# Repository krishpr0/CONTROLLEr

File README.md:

# CONTROLLER

CONTROLLER, IT is an Circuit which allows any type of SSD/HDD of a laptop size which is 2.5 inch Memory be a External Storage. This Project main chip is the ASM2464PD due to its high speed transfer speed. This chip was selected due to its support of USB4/Thunderbolt.

## What is this Project?
Controller is a high speed transfer external circuit board which is meant to make any 2.5 inch hard drive or ssd into an external Storage system. This unlocks the ability to make our own external storage system rather then buying it from outside. 

## How do we use Controller?
- First of all there are 4 screws on the side 2 on each unscrew it!
- Then pull of the top cover off the base plate.
- Then insert and slide in the HDD/SSD onto the PCIe connector.
- Place the cover plate back on and then tighten the screw 2 on each side this should secure the storage as well as the top case.
- Then connect to the computer that's it!
- (*NOTE: SOME MAY REQUIRE TO FLASH A FIRMWARE*)

## The reason for building this
Nowadays the software programs are increasing in size and as the phoots, videos we click also getting bigger and bigger. In my case each of my photos clicked is more than 5MB so that storage would rlly quickly fill up and I had to either delete it or buy an external drive and store it there.!

And so I choose the 2nd opt buy and external drive to store it cuz why delete photos which is memoory.!
So yeh like that it went on for years and years pile of drives js filled with photos, videos and files but now the storage are getting more expensier and also the casing used to hold the drive. !

SO i was really frustraied atp And i thought abt is there a way to make a good external drive !?
SO that was the reason i started this project due to the rise in price of storage due to AI>
T-T

## CAD

## CIRCUIT DIAGRAM: 

## PCB

## PCB 3D

# BOM
| #  | Reference                             | Value                                    | Footprint                       | Qty | Unit (USD) | Total (USD) | Datasheet / Link                                                                              |
|----|---------------------------------------|------------------------------------------|---------------------------------|-----|------------|-------------|-----------------------------------------------------------------------------------------------|
| 1  | U1                                    | ASM2464PD  USB4 Host Controller          | ASM2464PD                       | 1   | $8.000     | $8.000      | https://www.asmedia.com.tw/product/aGaq3YfSP5Yrq0T0/cGaq7XeSw9YRQ5T1                          |
| 2  | U2                                    | SPI Flash  SOIC-8  (Firmware storage)    | SOIC-8_5.3x5.3mm_P1.27mm        | 1   | $3         | $3          | http://ww1.microchip.com/downloads/en/DeviceDoc/21832H.pdf                                    |
| 3  | U3                                    | SPI Flash  DFN-8  (Firmware storage)     | DFN-8-1EP_3x2mm_P0.5mm          | 1   | $3         | $3          | http://ww1.microchip.com/downloads/en/DeviceDoc/21832H.pdf                                    |
| 4  | Y1                                    | 25MHz Crystal  SMD 3225-4Pin             | Crystal_SMD_3225-4Pin_3.2x2.5mm | 1   | $0.350     | $0.350      | https://au.rs-online.com/web/p/crystal-units/9047531                                          |
| 5  | J1                                    | USB-C Receptacle  Amphenol 12401610E4-2A | USB_C_Receptacle_Amphenol       | 1   | $1.200     | $1.200      | https://www.usb.org/sites/default/files/documents/usb_type-c.zip                              |
| 6  | J2                                    | SPI Header  2x04  2.54mm                 | PinHeader_2x04                  | 1   | $0.100     | $0.100      | ---                                                                                           |
| 7  | J3                                    | PCIe x4 Connector  THT Open              | PCIe_x4_tht_open                | 1   | $1.500     | $1.500      | http://www.ritrontek.com/uploadfile/2016/1026/20161026105231124.pdf                           |
| 8  | J4                                    | Chip Annoyers Header  2x02  2.54mm       | PinHeader_2x02                  | 2   | $0.10      | $0.10       | https://www.digikey.com/en/products/detail/harwin-inc/M20-9990246/3728226                     |
| 9  | J5                                    | UART Header  1x04  2.54mm                | PinHeader_1x04                  | 1   | $0.10      | $0.050      | https://www.digikey.com/en/products/detail/jst-sales-america-inc/B4B-XH-A/1651047             |
| 10 | J6                                    | I2C Header  1x04  2.54mm                 | PinHeader_1x04                  | 1   | $0.10      | $0.050      | https://www.digikey.com/en/products/detail/jst-sales-america-inc/B4B-XH-A/1651047             |
| 11 | J7,J8,J9,J10                          | 1x06 Header  1.27mm  x4                  | PinHeader_1x06                  | 4   | $0.20      | $0.200      | https://www.digikey.in/en/products/detail/jst-sales-america-inc/B6B-PH-K-S/926615             |
| 12 | R1,R2,R20,R24,R26,R29,R39,R41,R42,R43 | 1k ohm  0402                             | R_0402_1005Metric               | 10  | $0.15      | $1.50       | https://www.digikey.com.au/en/products/detail/yageo/RC0402FR-071KL/726513                     |
| 13 | R3,R4,R5,R6,R7,R8,R25,R30,R31         | 0 ohm  0402                              | R_0402_1005Metric               | 9   | $0.15      | $1.35       | https://www.digikey.com.au/en/products/detail/yageo/RC0402JR-070RL/726406                     |
| 14 | R9,R27,R28,R35,R38,R34,R36,R37        | 4.7k ohm  0402                           | R_0402_1005Metric               | 8   | $0.15      | $0.75       | https://www.digikey.com.au/en/products/detail/yageo/RC0402JR-074K7L/726477                    |
| 15 | R10,R21,R22, R23                      | 10k ohm  0402                            | R_0201_0603Metric               | 4   | $0.15      | $0.60       | https://www.digikey.com.au/en/products/detail/vishay-dale/CRCW040210K0FKED/1178121            |
| 16 | R11,R12,R13,R14,R15,R16,R17,R18       | 220k ohm  0201                           | R_0201_0603Metric               | 8   | $0.15      | $1.20       | https://www.digikey.com/en/products/detail/yageo/RC0201JR-07220KP/15219948                    |
| 19 | R32                                   | 12.1k ohm  0402                          | R_0402_1005Metric               | 1   | $0.10      | $0.10       | https://www.digikey.in/en/products/detail/yageo/RC0402FR-1012K1L/17020868                     |
| 20 | R33                                   | 100k ohm  0402                           | R_0402_1005Metric               | 1   | $0.20      | $0.20       | https://www.digikey.com/en/products/detail/yageo/AT0402BRD07100KL/5138605                     |
| 22 | C1                                    | 10pF  0402                               | C_0402_1005Metric               | 1   | $0.10      | $0.10       | https://www.digikey.com/en/products/detail/yageo/CC0402JRNPO8BN100/5883266                    |
| 23 | C2,C3,C4,C5,C6,C7,C8,C9               | 330nF  0201                              | C_0201_0603Metric               | 8   | $0.10      | $0.80       | https://www.mouser.in/ProductDetail/Walsin/0201X334M6R3CT?qs=iLbezkQI%252Bsj6TtN1Mk8apQ%3D%3D |
| 24 | C10,C21                               | 1uF  0402                                | C_0402_1005Metric               | 2   | $0.01      | $0.02       | https://robu.in/product/1uf-capacitor-smdc-0402-pack-of-50/                                   |
| 25 | C11                                   | 220pF  0402  DNP                         | C_0402_1005Metric               | 1   | $0.10      | $0.10       | https://www.digikey.com/en/products/detail/yageo/CC0402GRNPO9BN221/5883253                    |
| 26 | C12,C13,C14,C15,C16,C17,C18,C19       | 220nF  0402                              | C_0402_1005Metric               | 8   | $0.003     | $0.024      | https://www.lcsc.com/product-detail/C2649521.html                                             |
| 27 | C20                                   | 100nF  0402                              | C_0402_1005Metric               | 1   | $0.003     | $0.003      | https://www.lcsc.com/product-detail/C60474.html                                               |
| 28 | D1,D2,D3,D4,D5,D6,D7,D8               | Diode  0201  DNP                         | D_0201_0603Metric               | 8   | $0.32      | $2.56       | https://www.digikey.in/en/products/detail/kyocera-avx/GG020105100N2P/6826542                  |
| 29 | D9,D10,D11,D12,D13,D14,D15,D16        | LED  0603                                | LED_0603_1608Metric             | 8   | $0.01      | $0.08       | https://www.lcsc.com/product-detail/C19171390.html                                            |
|    | TOTAL                                 |                                          |                                 |     |            | 15.462      |                                                                                               |

# HOW TO BUILD

## What you need
-  Soldering Iron
-  Soldering wire
-  Flux
-  Multimeter
-  USB-C Cable

### Assembly Order
1. Solder all SMD Passives first (Resistors, Capacitors)
2. Solder ICs
3. Solder USB-C
4. Connect the PCIe Connecotr
5. Connect the Drive
6. Plug and Transfer.

### Firmware Setup 
- Open the 'firmware/src' - Upload the whole program to the SPI
- RUN

# Feature
- 1MB ROM
- SPI
- 40 GBPS USB Transfer Speed
- USB4/Thuerbolt Support
- HHD/SSD/NVMe support
- USB-C
- Power effiecent

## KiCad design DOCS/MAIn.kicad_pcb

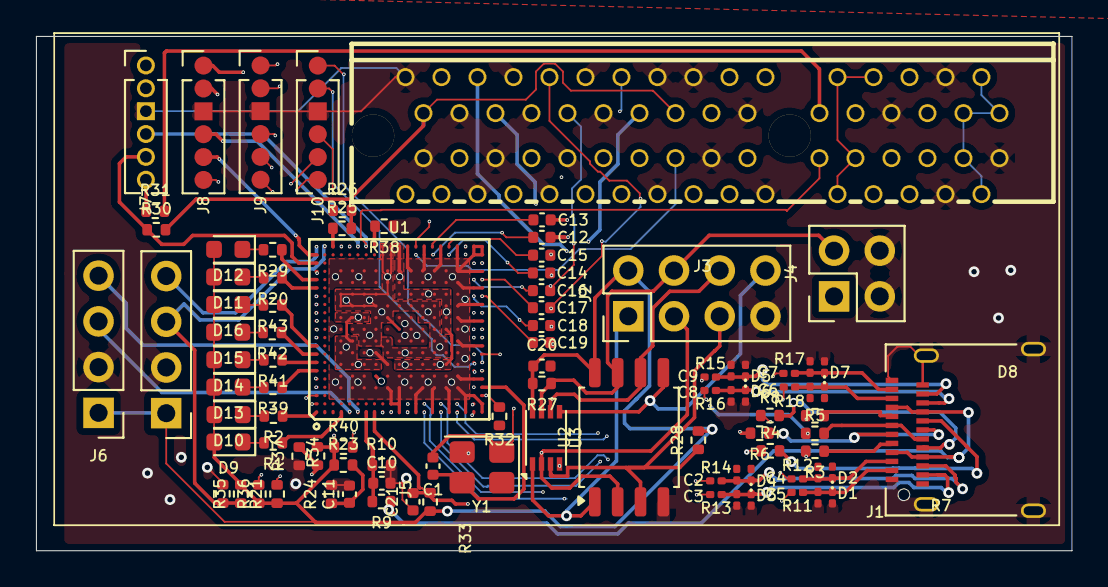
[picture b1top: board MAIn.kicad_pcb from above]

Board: 4 copper layers, 57.5 x 28.6 mm, 93 parts (0 on the bottom side), 118 nets.

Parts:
C1: 10p; C_0402_1005Metric
C2, C3, C4, C5, C6, C7, C8, C9: 0.33u; C_0201_0603Metric
C10, C21: 1u; C_0402_1005Metric
C11: 220p; C_0402_1005Metric
C12, C13, C14, C15, C16, C17, C18, C19: 0.22u; C_0402_1005Metric
C20: 0.1u; C_0402_1005Metric
D1, D2, D3, D4, D5, D6, D7, D8: D_0201_0603Metric
D9, D10, D11, D12, D13, D14, D15, D16: LED_0603_1608Metric
J1: USB_C_Receptacle; USB_C_Receptacle_Amphenol_12401610E4-2A
J2: SPIheader; PinHeader_2x04_P2.54mm_Vertical
J3: Bus_PCI_Express_x4; PCIe_x4_tht_open
J4: chip-annoyers; PinHeader_2x02_P2.54mm_Vertical
J5: UART; PinHeader_1x04_P2.54mm_Vertical
J6: I2C; PinHeader_1x04_P2.54mm_Vertical
J7, J8, J9, J10: Conn_01x06; PinHeader_1x06_P1.27mm_Vertical
R1, R2, R20, R24, R26, R29, R39, R41, R42, R43: 1k; R_0402_1005Metric
R3, R4, R5, R6, R7, R8, R25, R30, R31, R40: 0Ω; R_0402_1005Metric
R9, R27, R28, R34, R35, R36, R37, R38: 4.7k; R_0402_1005Metric
R10, R21, R22, R23: 10k; R_0402_1005Metric
R11, R12, R13, R14, R15, R16, R17, R18: 220k; R_0201_0603Metric
R32: 12.1k; R_0402_1005Metric
R33: 100k; R_0402_1005Metric
U1: ASM2464PD
U2: SPI_SOIC-8; SOIC-8_5.3x5.3mm_P1.27mm
U3: SPI_DFN-8; DFN-8-1EP_3x2mm_P0.5mm_EP1.3x1.5mm
Y1: 25MHz; Crystal_SMD_3225-4Pin_3.2x2.5mm

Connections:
+3.3VA: R40.2, U1.H5 (VCCA33)
+3.3V_LDO: C20.1, D9.2 (A), D10.2 (A), D11.2 (A), D12.2 (A), D13.2 (A), D14.2 (A), D15.2 (A), D16.2 (A), J2.2, J5.1, J6.1, R21.1, R22.1, R23.1, R27.2, R28.2, R33.2, R34.2, R35.2, R40.1, U1.D6 (VCCH), U1.D8 (VCCH), U1.D9 (VCCH), U1.D13 (VCCH), U1.E6 (VCCH), U1.E8 (VCCH), U1.E9 (VCCH), U1.E13 (VCCH), U1.F6 (VCCH), U1.F13 (VCCH), U1.H6 (VCCH), U2.8 (VCC), U3.8 (VCC)
+3.3V_SSD: J3.A9 (+3.3V), J3.A10 (+3.3V), J3.B8 (+3.3V), J3.B10 (3.3Vaux)
+5V_VBUS: J1.A4 (VBUS), J1.A9 (VBUS), J1.B4 (VBUS), J1.B9 (VBUS), R9.1
/Main/CC1_C: J1.A5 (CC1), R3.1
/Main/CC2_C: J1.B5 (CC2), R4.1
/Main/PCIe_TX0_C+: C12.2, J3.B14 (PETp0)
/Main/PCIe_TX0_C-: C13.2, J3.B15 (PETn0)
/Main/PCIe_TX1_C+: C14.2, J3.B19 (PETp1)
/Main/PCIe_TX1_C-: C15.2, J3.B20 (PETn1)
/Main/PCIe_TX2_C+: C16.2, J3.B23 (PETp2)
/Main/PCIe_TX2_C-: C17.2, J3.B24 (PETn2)
/Main/PCIe_TX3_C+: C18.2, J3.B27 (PETp3)
/Main/PCIe_TX3_C-: C19.2, J3.B28 (PETn3)
/Main/SBU1_C: J1.A8 (SBU1), R7.1
/Main/SBU2_C: J1.B8 (SBU2), R8.1
/Main/URX0_C+: C3.1, D3.1 (A1), J1.B11 (RX1+), R13.1
/Main/URX0_C-: C2.1, D4.1 (A1), J1.B10 (RX1-), R14.1
/Main/URX1_C+: C7.1, D7.1 (A1), J1.A11 (RX2+), R17.1
/Main/URX1_C-: C6.1, D8.1 (A1), J1.A10 (RX2-), R18.1
/Main/USB2_C_D+: J1.A6 (D+), J1.B6 (D+), R6.1
/Main/USB2_C_D-: J1.A7 (D-), J1.B7 (D-), R5.1
/Main/UTX0_C+: C5.1, D1.1 (A1), J1.A2 (TX1+), R11.1
/Main/UTX0_C-: C4.1, D2.1 (A1), J1.A3 (TX1-), R12.1
/Main/UTX1_C+: C9.1, D5.1 (A1), J1.B2 (TX2+), R15.1
/Main/UTX1_C-: C8.1, D6.1 (A1), J1.B3 (TX2-), R16.1
ActLED1: R1.1, U1.D1 (NVMeACTLED1/GPIO0)
ActLED2: R2.1, U1.A1 (NVMeACTLED2/GPIO3)
ActLED3: R20.1, U1.A16 (NVMeACTLED3/GPIO25)
ActLED4: R29.1, U1.A17 (NVMeACTLED4/GPIO26)
CC1: R3.2, U1.AA6 (CC1)
CC2: R4.2, U1.Y6 (CC2)
CLKREQ0#: J7.5, R21.2, R30.1, U1.A19 (CLKREQ0#/GPIO8)
CLKREQ1#: J8.5, U1.A20 (CLKREQ1#/GPIO14)
CLKREQ2#: J9.5, U1.A14 (CLKREQ2#/GPIO23)
CLKREQ3#: J10.5, U1.A15 (CLKREQ3#/GPIO24)
Card_SMBCLK: J3.B5 (SMCLK), J7.1
Card_SMBDAT: J3.B6 (SMDAT), J7.2
GND: C10.2, C11.2, C20.2, C21.1, D1.2 (A2), D2.2 (A2), D3.2 (A2), D4.2 (A2), D5.2 (A2), D6.2 (A2), D7.2 (A2), D8.2 (A2), J1.A1 (GND), J1.A12 (GND), J1.B1 (GND), J1.B12 (GND), J1.S1 (SHIELD), J2.7, J3.A1 (~PRSNT1), J3.A4 (GND), J3.A12 (GND), J3.A15 (GND), J3.A18 (GND), J3.A20 (GND), J3.A23 (GND), J3.A24 (GND), J3.A27 (GND), J3.A28 (GND), J3.A31 (GND), J3.B4 (GND), J3.B7 (GND), J3.B13 (GND), J3.B16 (GND), J3.B18 (GND), J3.B21 (GND), J3.B22 (GND), J3.B25 (GND), J3.B26 (GND), J3.B29 (GND), J3.B32 (GND), J4.3, J4.4, J5.2, J6.2, J7.3, J8.3, J9.3, J10.3, R10.2, R11.2, R12.2, R13.2, R14.2, R15.2, R16.2, R17.2, R18.2, R24.2, R26.1, R32.2, R36.1, R37.1, R38.1, U1.AA1 (GNDA), U1.AA2 (GNDA), U1.AA5 (GNDA), U1.AA9 (GNDA), U1.AA12 (GNDA), U1.AA14 (GNDA), U1.AA16 (GNDA), U1.AA18 (GNDA), U1.AA20 (GNDA), U1.AA21 (GNDA), U1.D4 (GND), U1.D5 (GND), U1.D11 (GND), U1.D17 (GND), U1.D18 (GND), U1.E4 (GND), U1.E5 (GND), U1.E17 (GND), U1.E18 (GND), U1.F4 (GND), U1.F5 (GND), U1.F8 (GND), U1.F17 (GND), U1.F18 (GND), U1.H4 (GND), U1.H8 (GND), U1.H17 (GND), U1.H18 (GND), U1.J4 (GND), U1.J5 (GND), U1.J6 (GND), U1.J11 (GND), U1.K2 (GND), U1.L1 (GNDA), U1.L2 (GNDA), U1.L4 (GNDA), U1.L5 (GNDA), U1.L9 (GND), U1.L13 (GND), U1.M20 (GNDA), U1.M21 (GNDA), U1.N1 (GNDA), U1.N2 (GNDA), U1.N4 (GNDA), U1.N5 (GNDA), U1.N9 (GND), U1.N11 (GND), U1.N13 (GND), U1.N17 (GNDA), U1.N18 (GNDA), U1.P4 (GNDA), U1.P5 (GNDA), U1.P9 (GND), U1.P11 (GND), U1.P17 (GNDA), U1.P18 (GNDA), U1.P20 (GNDA), U1.P21 (GNDA), U1.R1 (GNDA), U1.R2 (GNDA), U1.T4 (GNDA), U1.T5 (GNDA), U1.T17 (GNDA), U1.T18 (GNDA), U1.T20 (GNDA), U1.T21 (GNDA), U1.U1 (GNDA), U1.U2 (GNDA), U1.U4 (GNDA), U1.U5 (GNDA), U1.U17 (GNDA), U1.U18 (GNDA), U1.V4 (GNDA), U1.V5 (GNDA), U1.V6 (GNDA), U1.V8 (GNDA), U1.V9 (GNDA), U1.V11 (GNDA), U1.V13 (GNDA), U1.V14 (GNDA), U1.V16 (GNDA), U1.V17 (GNDA), U1.V18 (GNDA), U1.V20 (GNDA), U1.V21 (GNDA), U1.W1 (GNDA), U1.W2 (GNDA), U1.Y3 (GNDA), U1.Y5 (GNDA), U1.Y9 (GNDA), U1.Y12 (GNDA), U1.Y14 (GNDA), U1.Y16 (GNDA), U1.Y18 (GNDA), U1.Y20 (GNDA), U1.Y21 (GNDA), U2.4 (GND), U3.4 (GND), Y1.2, Y1.4
GPIO19: J8.6, U1.A10 (PRSNT1#/GPIO19)
GPIO21: J9.6, U1.A12 (PRSNT2#/GPIO21)
GPIO27: J10.6, U1.A18 (PRSNT3#/GPIO27)
HDDPC: R25.1, U1.C21 (HDDPC)
HDD_PC_EN: R25.2, R26.2
I2C_CLK: J6.3, U1.E1 (I2C_CLK_P)
I2C_DATA: J6.4, U1.F1 (I2C_DATA_P)
unnamed: D9.1 (K), R1.2
unnamed: D10.1 (K), R2.2
unnamed: D11.1 (K), R20.2
unnamed: D12.1 (K), R29.2
unnamed: D13.1 (K), R39.2
unnamed: D14.1 (K), R41.2
unnamed: D15.1 (K), R42.2
unnamed: D16.1 (K), R43.2
unnamed: J3.A2 (+12V), J3.A3 (+12V), J3.B1 (+12V), J3.B2 (+12V), J3.B3 (+12V)
unnamed: J3.B17 (~PRSNT2), J3.B31 (~PRSNT2), R30.2
unnamed: J3.B11 (~WAKE), R31.2
P1_LED: R39.1, U1.A6 (P1_LED/GPIO15)
P2_LED: R41.1, U1.A7 (P2_LED/GPIO16)
P3_LED: R42.1, U1.A8 (P3_LED/GPIO17)
P4_LED: R43.1, U1.A9 (P4_LED/GPIO18)
PCIe_RX0+: J3.A16 (PERp0), U1.N21 (PRXP0)
PCIe_RX0-: J3.A17 (PERn0), U1.N20 (PRXN0)
PCIe_RX1+: J3.A21 (PERp1), U1.W21 (PRXP1)
PCIe_RX1-: J3.A22 (PERn1), U1.W20 (PRXN1)
PCIe_RX2+: J3.A25 (PERp2), U1.Y19 (PRXP2)
PCIe_RX2-: J3.A26 (PERn2), U1.AA19 (PRXN2)
PCIe_RX3+: J3.A29 (PERp3), U1.AA13 (PRXP3)
PCIe_RX3-: J3.A30 (PERn3), U1.Y13 (PRXN3)
PCIe_TX0+: C12.1, U1.R20 (PTXP0)
PCIe_TX0-: C13.1, U1.R21 (PTXN0)
PCIe_TX1+: C14.1, U1.U20 (PTXP1)
PCIe_TX1-: C15.1, U1.U21 (PTXN1)
PCIe_TX2+: C16.1, U1.Y17 (PTXP2)
PCIe_TX2-: C17.1, U1.AA17 (PTXN2)
PCIe_TX3+: C18.1, U1.Y15 (PTXP3)
PCIe_TX3-: C19.1, U1.AA15 (PTXN3)
PERST0#: C11.1, J3.A11 (~PERST), J7.4, R23.2, R24.1, U1.G21 (PERST0#)
PERST1#: J8.4, U1.F21 (NC/PERST1#)
PERST2#: J9.4, U1.E21 (NC/PERST2#)
PERST3#: J10.4, U1.D21 (NC/PERST3#)
PE_WAKE#: J7.6, R22.2, R31.1, U1.A13 (PE_WAKE#/GPIO22)
REFCLK1+: J8.1, U1.AA11 (NC/REFCLKP1)
REFCLK1-: J8.2, U1.Y11 (NC/REFCLKN1)
REFCLK2+: J9.1, U1.AA10 (NC/REFCLKP2)
REFCLK2-: J9.2, U1.Y10 (NC/REFCLKN2)
REFCLK3+: J10.1, U1.AA7 (NC/REFCLKP3)
REFCLK3-: J10.2, U1.Y7 (NC/REFCLKN3)
REFCLK+: J3.A13 (REFCLK+), U1.AA8 (REFCLKP0)
REFCLK-: J3.A14 (REFCLK-), U1.Y8 (REFCLKN0)
RST#: C21.2, J4.1, R33.1, U1.H1 (RST#)
SBU1: R7.2, U1.K1 (SBU1)
SBU2: R8.2, U1.J1 (SBU2)
SPI_CLK: J2.6, U1.A5 (GPIO6/SPI_CLK), U2.6 (SCK), U3.6 (SCK)
SPI_CS#: J2.1, U1.A2 (GPIO4/SPI_CS#), U2.1 (~CS), U3.1 (~CS)
SPI_DI: J2.3, U1.A4 (GPIO7/SPI_DI), U2.2 (MISO), U3.2 (MISO)
SPI_DO: J2.8, R34.1, R37.2, U1.A3 (GPIO5/SPI_DO), U2.5 (MOSI), U3.5 (MOSI)
SPI_HOLD#: J2.4, J4.2, R27.1, U2.7 (~HOLD), U3.7 (~HOLD)
SPI_WP#: J2.5, R28.1, U2.3 (~WP), U3.3 (~WP)
TEST_EN: R38.2, U1.H21 (TEST_EN)
UART_RX: J5.4, U1.A21 (PRSNT0#/UART_RX)
UART_TX: J5.3, R35.1, R36.2, U1.B21 (MEMREPAIR/UART_TX)
UREXT: R32.1, U1.AA3 (REXT)
URX0+: C3.2, U1.P1 (URXP0)
URX0-: C2.2, U1.P2 (URXN0)
URX1+: C7.2, U1.Y2 (URXP1)
URX1-: C6.2, U1.Y1 (URXN1)
USB2_D+: R6.2, U1.M1 (UDP)
USB2_D-: R5.2, U1.M2 (UDM)
UTX0+: C5.2, U1.T1 (UTXP0)
UTX0-: C4.2, U1.T2 (UTXN0)
UTX1+: C9.2, U1.V2 (UTXP1)
UTX1-: C8.2, U1.V1 (UTXN1)
VBUS: C10.1, R9.2, R10.1, U1.G1 (VBUS)
VCCL: U1.L6 (VCCL), U1.L16 (VCCL), U1.L17 (VCCL), U1.L18 (VCCL), U1.L20 (VCCL), U1.L21 (VCCL), U1.N6 (VCCL), U1.N16 (VCCL), U1.P6 (VCCL), U1.P16 (VCCL), U1.T6 (VCCL), U1.T16 (VCCL), U1.U6 (VCCL), U1.U11 (VCCL), U1.U13 (VCCL), U1.U14 (VCCL), U1.U16 (VCCL)
VDD: U1.D14 (VDD), U1.D16 (VDD), U1.E11 (VDD), U1.E14 (VDD), U1.E16 (VDD), U1.F9 (VDD), U1.F11 (VDD), U1.F14 (VDD), U1.F16 (VDD), U1.H9 (VDD), U1.H11 (VDD), U1.H13 (VDD), U1.H14 (VDD), U1.H16 (VDD), U1.J8 (VDD), U1.J9 (VDD), U1.J13 (VDD), U1.J14 (VDD), U1.J16 (VDD), U1.J17 (VDD), U1.J18 (VDD), U1.J20 (VDD), U1.J21 (VDD), U1.K20 (VDD), U1.K21 (VDD), U1.L8 (VDD), U1.L11 (VDD), U1.L14 (VDD), U1.N8 (VDD), U1.N14 (VDD), U1.P8 (VDD), U1.P13 (VDD), U1.P14 (VDD), U1.T8 (VDD), U1.T9 (VDD), U1.T11 (VDD), U1.T13 (VDD), U1.T14 (VDD), U1.U8 (VDD), U1.U9 (VDD)
XI: C1.2, U1.AA4 (XI), Y1.3
XO: C1.1, U1.Y4 (XO), Y1.1

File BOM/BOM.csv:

#,Reference,Value,Footprint,Qty,Unit (USD),Total (USD),Datasheet / Link
1,U1,ASM2464PD  USB4 Host Controller,ASM2464PD,1,$8.000,$8.000,https://www.asmedia.com.tw/product/aGaq3YfSP5Yrq0T0/cGaq7XeS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
2,U2,SPI Flash  SOIC-8  (Firmware storage),SOIC-8_5.3x5.3mm_P1.27mm,1,$3,$3,http://ww1.microchip.com/downloads/en/DeviceDoc/21832H.pdf
3,U3,SPI Flash  DFN-8  (Firmware storage),DFN-8-1EP_3x2mm_P0.5mm,1,$3,$3,http://ww1.microchip.com/downloads/en/DeviceDoc/21832H.pdf
4,Y1,25MHz Crystal  SMD 3225-4Pin,Crystal_SMD_3225-4Pin_3.2x2.5mm,1,$0.350,$0.350,https://au.rs-online.com/web/p/crystal-units/9047531
5,J1,USB-C Receptacle  Amphenol 12401610E4-2A,USB_C_Receptacle_Amphenol,1,$1.200,$1.200,https://www.usb.org/sites/default/files/documents/usb_type-c.zip
6,J2,SPI Header  2x04  2.54mm,PinHeader_2x04,1,$0.100,$0.100,---
7,J3,PCIe x4 Connector  THT Open,PCIe_x4_tht_open,1,$1.500,$1.500,http://www.ritrontek.com/uploadfile/2016/1026/20161026105231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
8,J4,Chip Annoyers Header  2x02  2.54mm,PinHeader_2x02,2,$0.10,$0.10,https://www.digikey.com/en/products/detail/harwin-inc/M20-99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
9,J5,UART Header  1x04  2.54mm,PinHeader_1x04,1,$0.10,$0.050,https://www.digikey.com/en/products/detail/jst-sales-america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
10,J6,I2C Header  1x04  2.54mm,PinHeader_1x04,1,$0.10,$0.050,https://www.digikey.com/en/products/detail/jst-sales-america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
11,"J7,J8,J9,J10",1x06 Header  1.27mm  x4,PinHeader_1x06,4,$0.20,$0.200,https://www.digikey.in/en/products/detail/jst-sales-america-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
12,"R1,R2,R20,R24,R26,R29,R39,R41,R42,R43",1k ohm  0402,R_0402_1005Metric,10,$0.15,$1.50,https://www.digikey.com.au/en/products/detail/yageo/RC0402FR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
13,"R3,R4,R5,R6,R7,R8,R25,R30,R31",0 ohm  0402,R_0402_1005Metric,9,$0.15,$1.35,https://www.digikey.com.au/en/products/detail/yageo/RC0402JR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
14,"R9,R27,R28,R35,R38,R34,R36,R37",4.7k ohm  0402,R_0402_1005Metric,8,$0.15,$0.75,https://www.digikey.com.au/en/products/detail/yageo/RC0402JR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
15,"R10,R21,R22, R23",10k ohm  0402,R_0201_0603Metric,4,$0.15,$0.60,https://www.digikey.com.au/en/products/detail/vishay-dale/CR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
16,"R11,R12,R13,R14,R15,R16,R17,R18",220k ohm  0201,R_0201_0603Metric,8,$0.15,$1.20,https://www.digikey.com/en/products/detail/yageo/RC0201JR-07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
19,R32,12.1k ohm  0402,R_0402_1005Metric,1,$0.10,$0.10,https://www.digikey.in/en/products/detail/yageo/RC0402FR-101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
20,R33,100k ohm  0402,R_0402_1005Metric,1,$0.20,$0.20,https://www.digikey.com/en/products/detail/yageo/AT0402BRD07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
22,C1,10pF  0402,C_0402_1005Metric,1,$0.10,$0.10,https://www.digikey.com/en/products/detail/yageo/CC0402JRNPO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
23,"C2,C3,C4,C5,C6,C7,C8,C9",330nF  0201,C_0201_0603Metric,8,$0.10,$0.80,https://www.mouser.in/ProductDetail/Walsin/0201X334M6R3CT?qs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
24,"C10,C21",1uF  0402,C_0402_1005Metric,2,$0.01,$0.02,https://robu.in/product/1uf-capacitor-smdc-0402-pack-of-50/
25,C11,220pF  0402  DNP,C_0402_1005Metric,1,$0.10,$0.10,https://www.digikey.com/en/products/detail/yageo/CC0402GRNPO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
26,"C12,C13,C14,C15,C16,C17,C18,C19",220nF  0402,C_0402_1005Metric,8,$0.003,$0.024,https://www.lcsc.com/product-detail/C2649521.html
27,C20,100nF  0402,C_0402_1005Metric,1,$0.003,$0.003,https://www.lcsc.com/product-detail/C60474.html
28,"D1,D2,D3,D4,D5,D6,D7,D8",Diode  0201  DNP,D_0201_0603Metric,8,$0.32,$2.56,https://www.digikey.in/en/products/detail/kyocera-avx/GG0201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
29,"D9,D10,D11,D12,D13,D14,D15,D16",LED  0603,LED_0603_1608Metric,8,$0.01,$0.08,https://www.lcsc.com/product-detail/C19171390.html
,TOTAL,,,,,15.462,

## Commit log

2026-06-19 completed:
